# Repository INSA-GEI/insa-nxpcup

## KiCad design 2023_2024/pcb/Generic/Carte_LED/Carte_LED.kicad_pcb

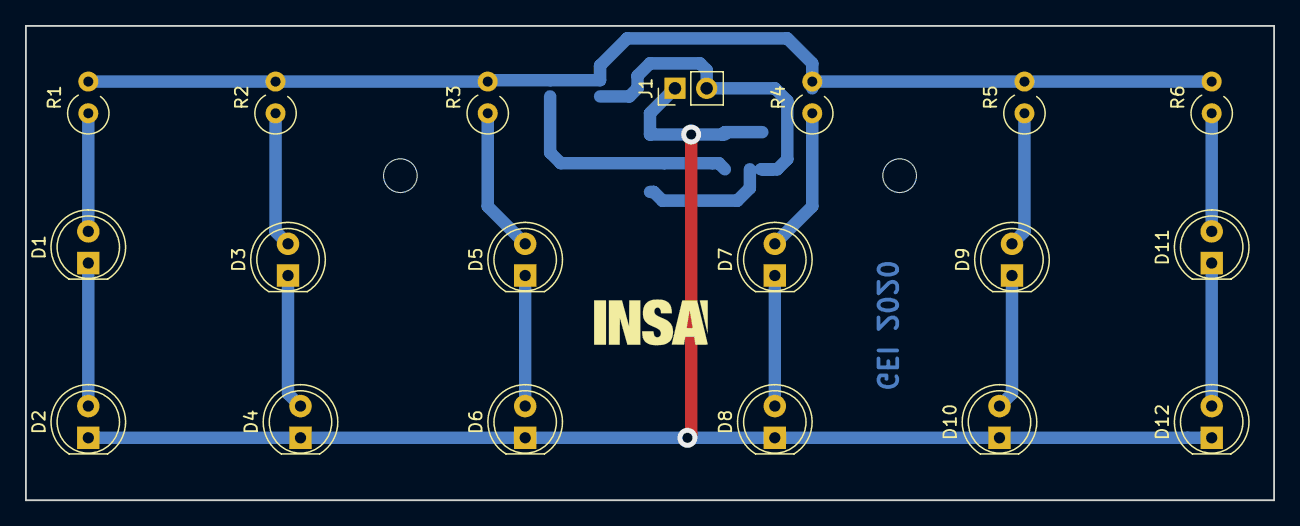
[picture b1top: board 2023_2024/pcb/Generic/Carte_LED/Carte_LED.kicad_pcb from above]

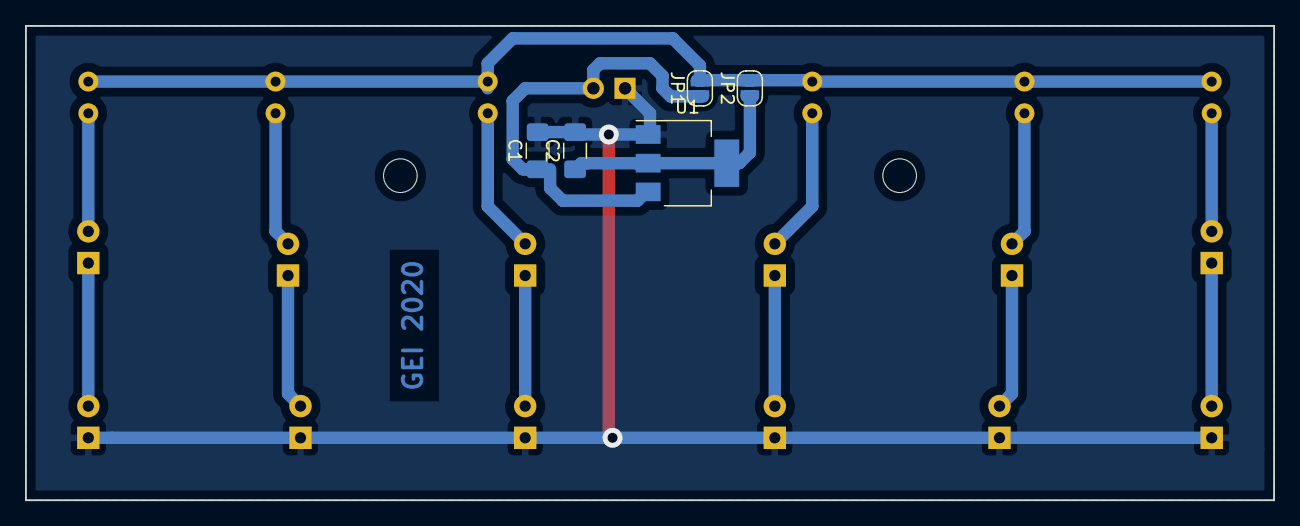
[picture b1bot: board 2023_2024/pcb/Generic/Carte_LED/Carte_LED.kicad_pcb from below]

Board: 2 copper layers, 100.0 x 38.0 mm, 27 parts (5 on the bottom side), 16 nets.

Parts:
C1, C2: 4.7µF; C_1206_3216Metric_Pad1.42x1.75mm_HandSolder
D1, D2, D3, D4, D5, D6, D7, D8, D9, D10, D11, D12: VLCS5830; LED_D5.0mm_Clear
G1: LOGO; insa-image
H1, H2: MountingHole; MountingHole_2.7mm_M2.5
J1: Conn_01x02; PinHeader_1x02_P2.54mm_Vertical
JP1, JP2: SolderJumper_2_Open; SolderJumper-2_P1.3mm_Open_RoundedPad1.0x1.5mm
R1, R2, R3, R4, R5, R6: 0R; R_Axial_DIN0309_L9.0mm_D3.2mm_P2.54mm_Vertical
U1: ZLDO1117G50TA; SOT-223-3_TabPin2

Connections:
+5V: JP1.2, JP2.2, R1.2, R2.2, R3.2, R4.2, R5.2, R6.2
+BATT: C1.1, J1.2, JP1.1, U1.3
GND: C1.2, C2.2, D2.1, D4.1, D6.1, D8.1, D10.1, D12.1, J1.1, U1.1
unnamed: C2.1, JP2.1, U1.2
unnamed: D1.1, D2.2
unnamed: D1.2, R1.1
unnamed: D3.1, D4.2
unnamed: D3.2, R2.1
unnamed: D5.1, D6.2
unnamed: D5.2, R3.1
unnamed: D7.1, D8.2
unnamed: D7.2, R4.1
unnamed: D9.2, R5.1
unnamed: D9.1, D10.2
unnamed: D11.1, D12.2
unnamed: D11.2, R6.1

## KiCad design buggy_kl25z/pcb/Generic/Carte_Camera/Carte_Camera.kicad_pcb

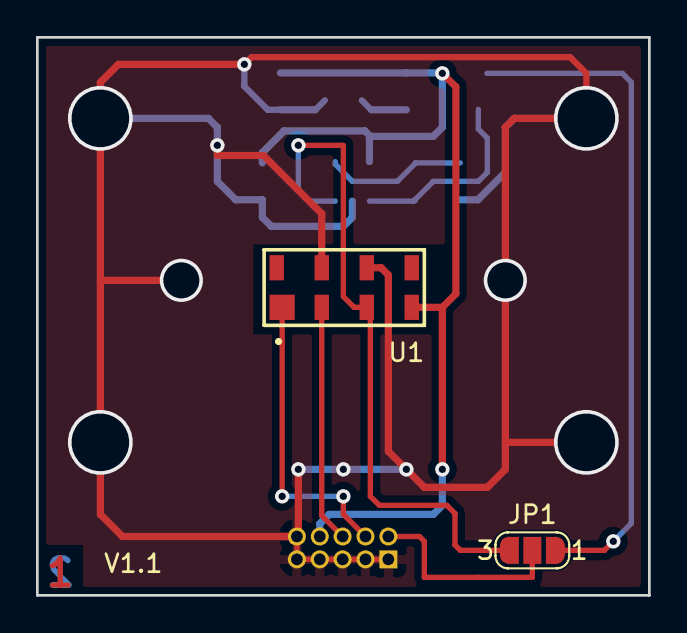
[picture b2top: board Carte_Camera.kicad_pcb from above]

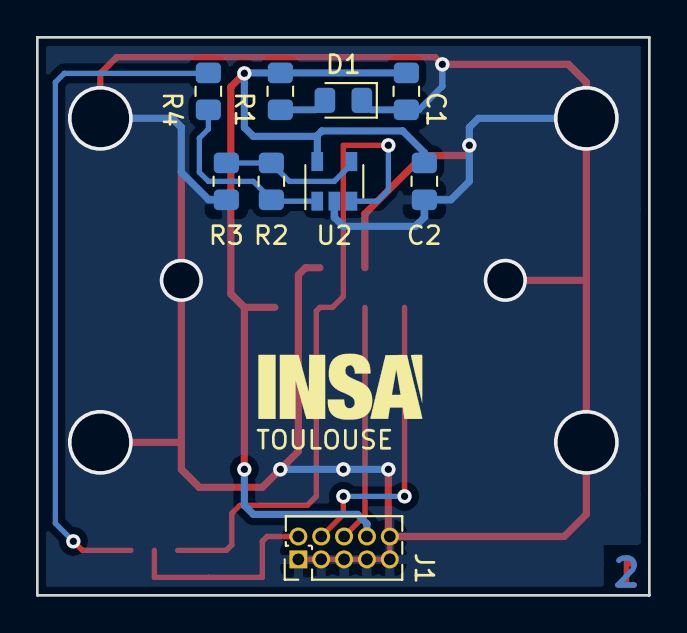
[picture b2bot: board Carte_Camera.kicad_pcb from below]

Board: 2 copper layers, 34.0 x 31.0 mm, 12 parts (10 on the bottom side), 10 nets.

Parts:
C1, C2: 1µF; C_0805_2012Metric_Pad1.15x1.40mm_HandSolder
D1: LED; LED_0805_2012Metric_Pad1.15x1.40mm_HandSolder
G1: LOGO; insa-image
J1: Samtec FTS-105-01-L-DV; PinHeader_2x05_P1.27mm_Vertical
JP1: SolderJumper_3_Open; SolderJumper-3_P1.3mm_Open_RoundedPad1.0x1.5mm_NumberLabels
R1: 680R; R_0805_2012Metric_Pad1.15x1.40mm_HandSolder
R2, R3: 1K; R_0805_2012Metric_Pad1.15x1.40mm_HandSolder
R4: 0; R_0805_2012Metric_Pad1.15x1.40mm_HandSolder
U1: TSL1401CL
U2: TSV911AILT; SOT-23-5

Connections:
+3V3: C1.1, C2.1, J1.8, R1.1, U1.4, U2.5
/CCD_AO: J1.2, JP1.2
/CCD_CLK: J1.6, U1.2
/CCD_SI: J1.4, U1.1
GND: C1.2, C2.2, D1.1, J1.1, J1.3, J1.5, J1.7, J1.9, J1.10, R3.2, U1.6, U1.7, U2.2
unnamed: D1.2, R1.2
unnamed: JP1.1, R4.2
unnamed: JP1.3, U1.3, U2.3
unnamed: R2.1, R3.1, U2.4
unnamed: R2.2, R4.1, U2.1

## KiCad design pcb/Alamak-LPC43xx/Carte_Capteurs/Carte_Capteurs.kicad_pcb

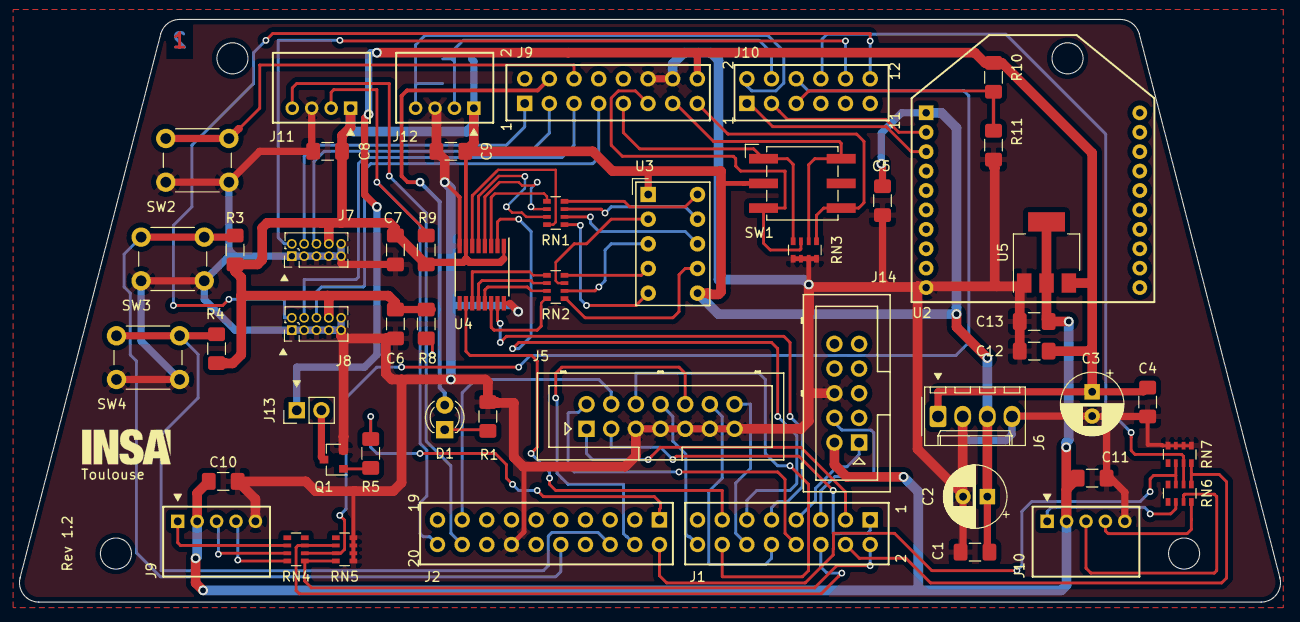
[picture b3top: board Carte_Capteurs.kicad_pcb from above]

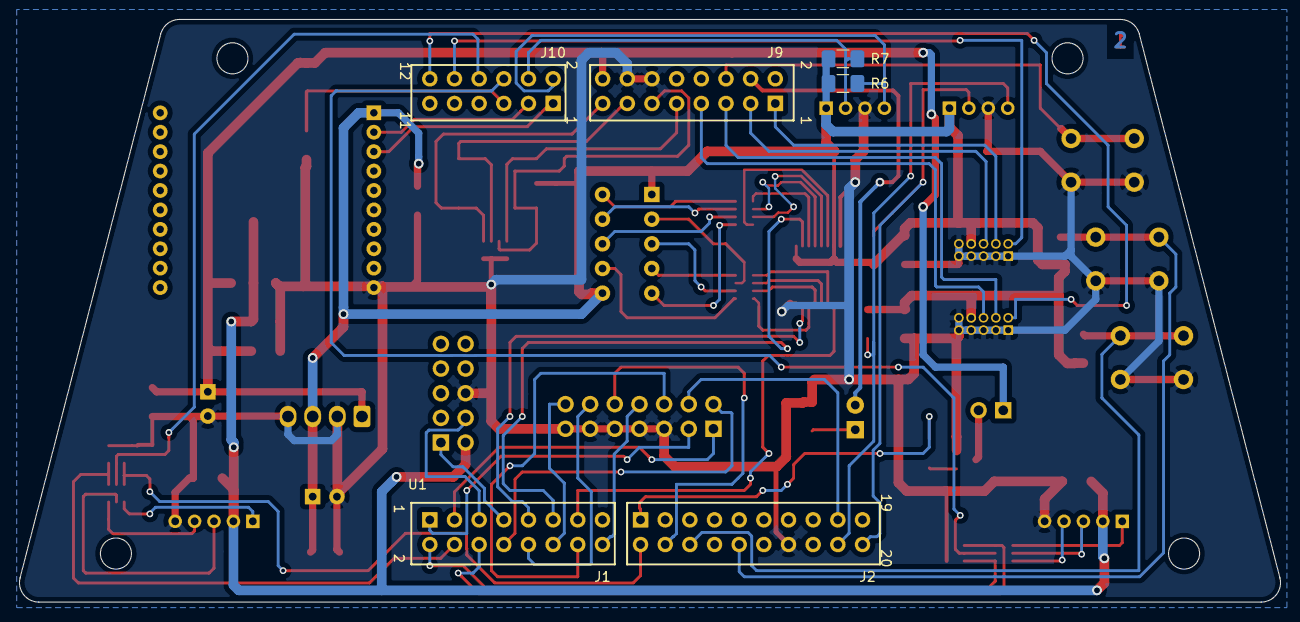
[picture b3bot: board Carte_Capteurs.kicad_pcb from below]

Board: 2 copper layers, 129.9 x 60.0 mm, 52 parts (3 on the bottom side), 71 nets.

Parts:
C1, C4, C5, C6, C7, C8, C9, C10, C11: 100nF; C_1206_3216Metric_Pad1.42x1.75mm_HandSolder
C2, C3: 100µF; CP_Radial_D6.3mm_P2.50mm
C12, C13: 4.7µF; C_1206_3216Metric_Pad1.42x1.75mm_HandSolder
D1: LED; LED_D3.0mm
J5: Conn_02x07_Odd_Even; Multicomp_MC9A12-1434_2x07_P2.54mm_Vertical
J6: Molex KK 254; Molex_KK-254_AE-6410-04A_1x04_P2.54mm_Vertical
J7, J8: Samtec FTS-105-01-L-DV; PinHeader_2x05_P1.27mm_Vertical
J9, J10: DF3A-5P-2DS
J11, J12: DF3A-4P-2DS
J13: Conn_01x02; PinHeader_1x02_P2.54mm_Vertical
J14: Conn_02x05_Odd_Even; Multicomp_MC9A12-1034_2x05_P2.54mm_Vertical
Logo1: LOGO; insa-image
Q1: NTR3C21NZT1G; SOT-23
R1, R5: 100R; R_1206_3216Metric_Pad1.42x1.75mm_HandSolder
R3, R4: 10K; R_1206_3216Metric_Pad1.42x1.75mm_HandSolder
R6, R7, R8, R9, R10: 4.7K; R_1206_3216Metric_Pad1.42x1.75mm_HandSolder
R11: 2.2K; R_1206_3216Metric_Pad1.42x1.75mm_HandSolder
RN1, RN2: 220R; R_Array_Convex_4x0603
RN3: 10K; R_Array_Convex_4x0603
RN4, RN6: 2.2K; R_Array_Convex_4x0603
RN5, RN7: 3.3K; R_Array_Convex_4x0603
SW1: SMR8016C-1; Nidec_Copal_SMR-8016C
SW2: Reset; SW_PUSH_6mm_H4.3mm
SW3: USER1; SW_PUSH_6mm_H4.3mm
SW4: USER2; SW_PUSH_6mm_H4.3mm
U1: FRDM-KL25Z
U2: XBee; Xbee3
U3: HDSP-7501; HDSP-A151
U4: TCL6C598; TSSOP-16_4.4x5mm_P0.65mm
U5: ZLDO1117G50TA; SOT-223-3_TabPin2

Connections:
+3V3: C1.1, C2.1, C5.1, C6.1, C7.1, C8.1, C9.1, J6.3, J7.8, J8.8, J11.1, J12.1, R3.1, R4.1, R6.2, R7.2, R8.2, R9.2, SW1.C, U2.1, U3.1, U3.6, U4.1, U4.7
+5V: C10.1, C11.1, C13.1, J9.2, J10.2, J14.2, U5.2
+BATT: C3.1, C4.1, C12.1, J6.1, J13.1, R10.1, U1.3.16, U5.3
/CAM_LED: R5.1, U1.2.1
/CCD_AD0: J7.2, U1.4.10
/CCD_AD1: J8.2, U1.4.12
/CCD_CLK0: J7.6, U1.3.3
/CCD_CLK1: J8.6, U1.3.7
/CCD_SI0: J7.4, U1.3.1
/CCD_SI1: J8.4, U1.3.5
/DISABLE_MOT_L: J5.1, U1.1.3
/DISABLE_MOT_R: J5.3, U1.1.1
/DISP_CLK: U1.1.9, U4.15
/DISP_LATCH: U1.1.13, U4.10
/DISP_SIN: U1.1.11, U4.2
/ENC_INDEX1: RN4.3, RN5.6, U1.1.6
/ENC_INDEX2: RN6.3, RN7.6, U1.2.2
/ENC_SIG_A1: RN4.2, RN5.7, U1.4.6
/ENC_SIG_A2: RN6.2, RN7.7, U1.4.8
/ENC_SIG_B1: RN4.1, RN5.8, U1.1.2
/ENC_SIG_B2: RN6.1, RN7.8, U1.1.4
/FEEDBACK_MOT_L: J5.4, U1.2.17
/FEEDBACK_MOT_R: J5.10, U1.2.4
/PIXY2_RX: J14.1, U1.1.7
/PIXY2_TX: J14.4, U1.1.5
/PWM_MOT_L_1: J5.6, U1.1.14
/PWM_MOT_L_2: J5.8, U1.1.16
/PWM_MOT_R_1: J5.12, U1.1.10
/PWM_MOT_R_2: J5.14, U1.1.12
/PWR_LED: D1.2, U1.3.4
/RESET: SW2.2, U1.3.6
/ROT_SW_1: RN3.8, SW1.1, U1.3.9
/ROT_SW_2: RN3.7, SW1.2, U1.3.11
/ROT_SW_4: RN3.6, SW1.4, U1.3.13
/ROT_SW_8: RN3.5, SW1.8, U1.3.15
/SENS_SCL1: J11.4, R8.1, U1.2.18
/SENS_SCL2: J12.4, R6.1, U1.4.2
/SENS_SDA1: J11.2, R9.1, U1.2.20
/SENS_SDA2: J12.2, R7.1, U1.4.4
/SERVO_PWM: J5.2, U1.1.8
/SW_USER1: R3.2, SW3.2, U1.2.10
/SW_USER2: R4.2, SW4.2, U1.2.6
/USART_RX: U1.4.3, U2.2
/USART_TX: U1.4.1, U2.3
/VBAT_ADC: R10.2, R11.1, U1.4.5
GND: C1.2, C2.2, C3.2, C4.2, C5.2, C6.2, C7.2, C8.2, C9.2, C10.2, C11.2, C12.2, C13.2, J5.5, J5.7, J5.9, J5.11, J5.13, J6.2, J6.4, J7.1, J7.3, J7.5, J7.7, J7.9, J7.10, J8.1, J8.3, J8.5, J8.7, J8.9, J8.10, J9.5, J10.5, J11.3, J12.3, J14.6, Q1.2, R1.2, R11.2, RN3.1, RN3.2, RN3.3, RN3.4, RN5.1, RN5.2, RN5.3, RN5.4, RN7.1, RN7.2, RN7.3, RN7.4, SW2.1, SW3.1, SW4.1, U1.2.14, U1.3.12, U1.3.14, U2.10, U4.8, U4.16, U5.1
unnamed: D1.1, R1.1
unnamed: J9.1, RN4.6
unnamed: J9.3, RN4.7
unnamed: J9.4, RN4.8
unnamed: J10.1, RN6.6
unnamed: J10.3, RN6.7
unnamed: J10.4, RN6.8
unnamed: J13.2, Q1.3
unnamed: Q1.1, R5.2
unnamed: RN1.1, U3.5
unnamed: RN1.2, U3.8
unnamed: RN1.3, U3.9
unnamed: RN1.4, U3.10
unnamed: RN1.5, U4.3
unnamed: RN1.6, U4.4
unnamed: RN1.7, U4.5
unnamed: RN1.8, U4.6
unnamed: RN2.1, U3.7
unnamed: RN2.2, U3.3
unnamed: RN2.3, U3.2
unnamed: RN2.4, U3.4
unnamed: RN2.5, U4.11
unnamed: RN2.6, U4.12
unnamed: RN2.7, U4.13
unnamed: RN2.8, U4.14

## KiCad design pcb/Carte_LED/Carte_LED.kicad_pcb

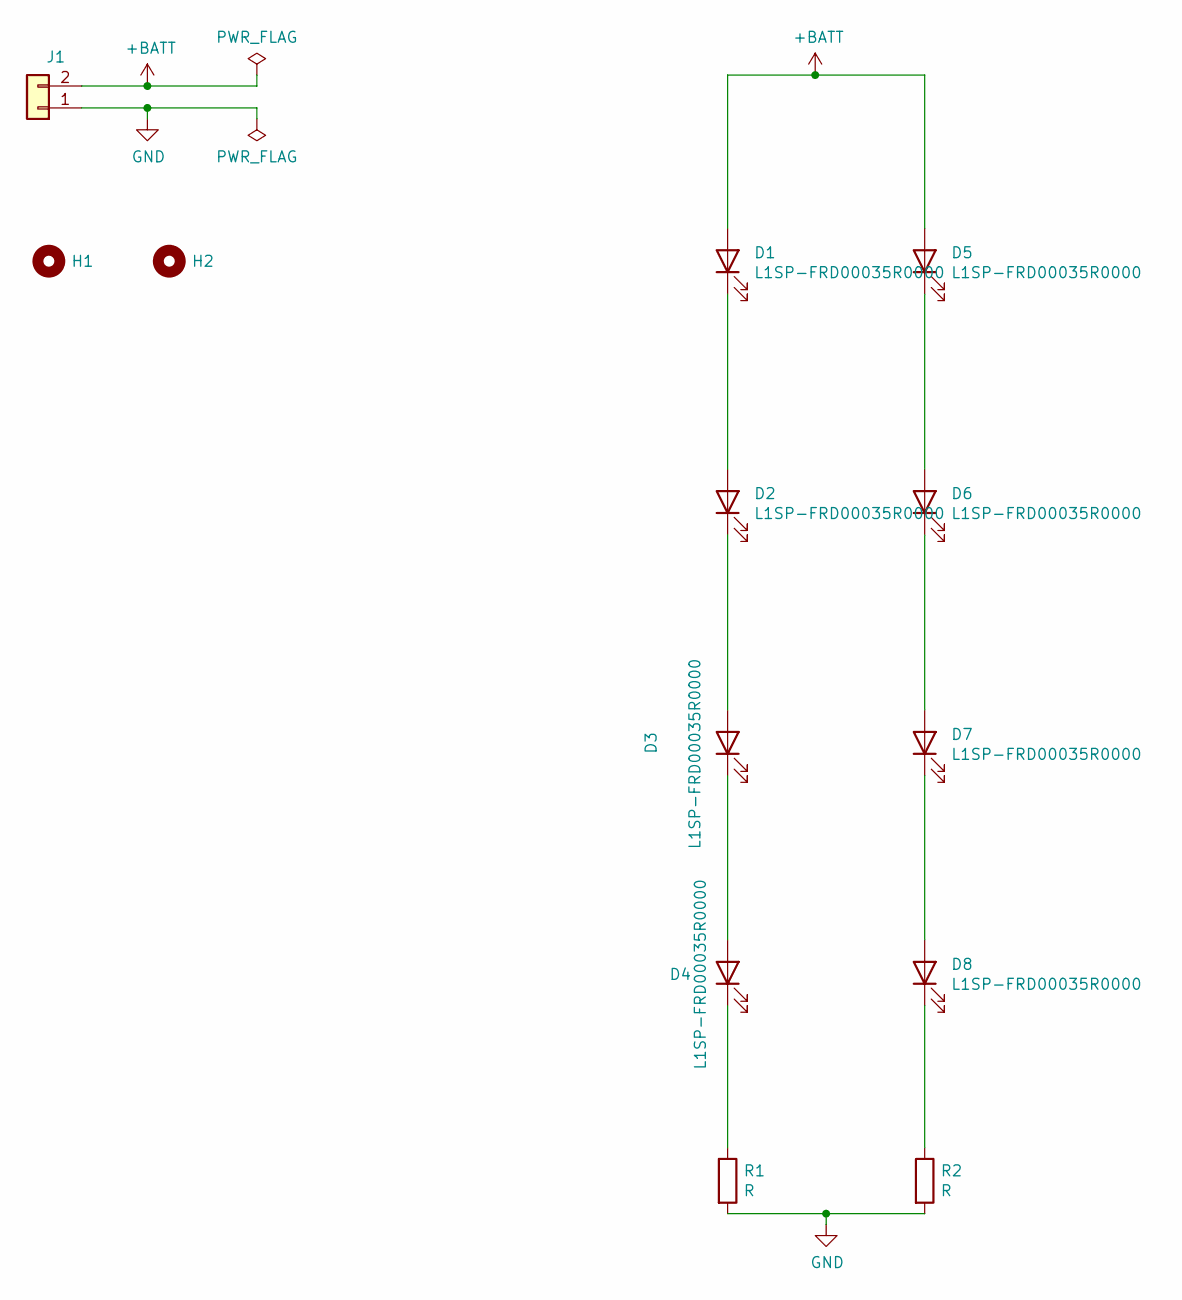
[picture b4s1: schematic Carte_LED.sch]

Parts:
D1, D2, D3, D4, D5, D6, D7, D8: L1SP-FRD00035R0000; LED_PLCC_2835_Handsoldering
H1, H2: MountingHole; MountingHole_2.7mm_M2.5
J1: Conn_01x02; PinHeader_1x02_P2.54mm_Vertical
R1, R2: R; R_Axial_DIN0309_L9.0mm_D3.2mm_P12.70mm_Horizontal

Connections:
+BATT: D1.2 (A), D5.2 (A), J1.2
GND: J1.1, R1.2, R2.2
unnamed: D1.1 (K), D2.2 (A)
unnamed: D2.1 (K), D3.2 (A)
unnamed: D3.1 (K), D4.2 (A)
unnamed: D4.1 (K), R1.1
unnamed: D5.1 (K), D6.2 (A)
unnamed: D6.1 (K), D7.2 (A)
unnamed: D7.1 (K), D8.2 (A)
unnamed: D8.1 (K), R2.1

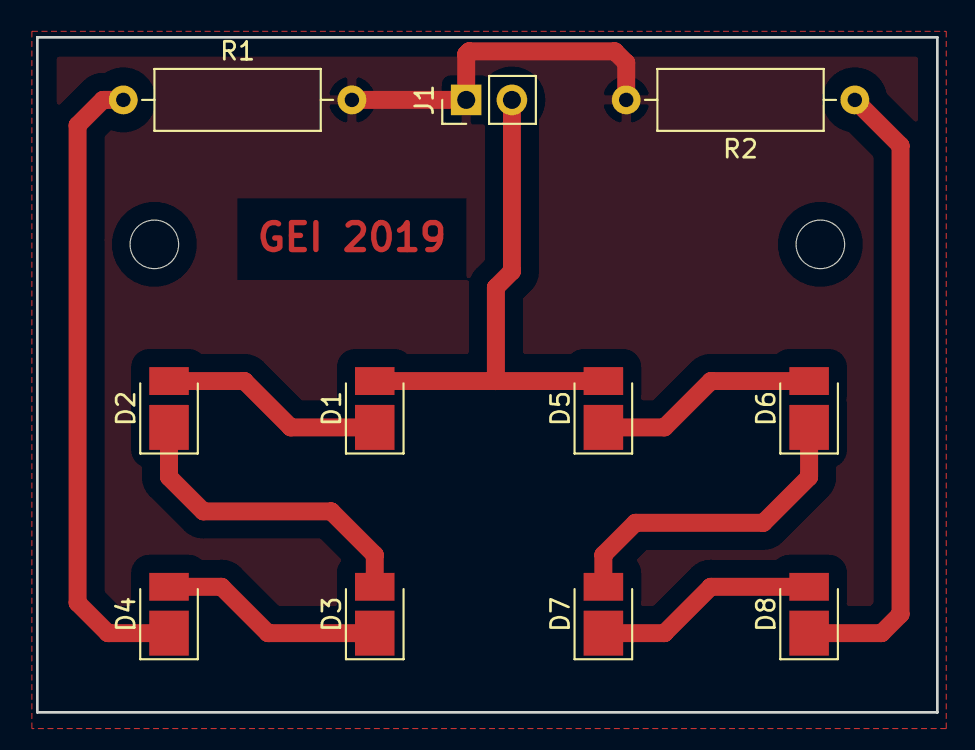
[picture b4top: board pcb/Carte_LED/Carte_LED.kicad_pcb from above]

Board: 2 copper layers, 50.0 x 37.5 mm, 13 parts (0 on the bottom side), 10 nets.
